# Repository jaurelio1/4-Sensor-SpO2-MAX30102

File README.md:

# 8-Modulo-I2C-OLED
Repositório da disciplina de Sistemas Embarcados do projeto de 8 Modulo I2C OLED

Alunos:

José Aurélio

Wesley Palmeira

Eduardo Donato

O projeto tem o intuito de desenvolver um despertador fazendo o uso dos módulos I2C OLED e RTC DS3231 Utilizando o RTC(Real Time Clock) DS3231 que é um relógio em tempo real de alta precisão e baixo consumo de energia, podendo fornecer informações de hora, segundos, dia, mês e ano, junto com uma bateria CR2032 para permitir o armazenamentos dos dados mesmo com a falta de energia, evitando que dados sejam perdidos; O ATmega32u4 como microcontrolador; o SSD1306 display OLED com o módulo I2C;

Utilizaremos como base as bibliotecas colocadas na pasta libraries para desenvolver a nossa (conexão do ATmega32u4, com o Display OLED e o RTC DS3231)

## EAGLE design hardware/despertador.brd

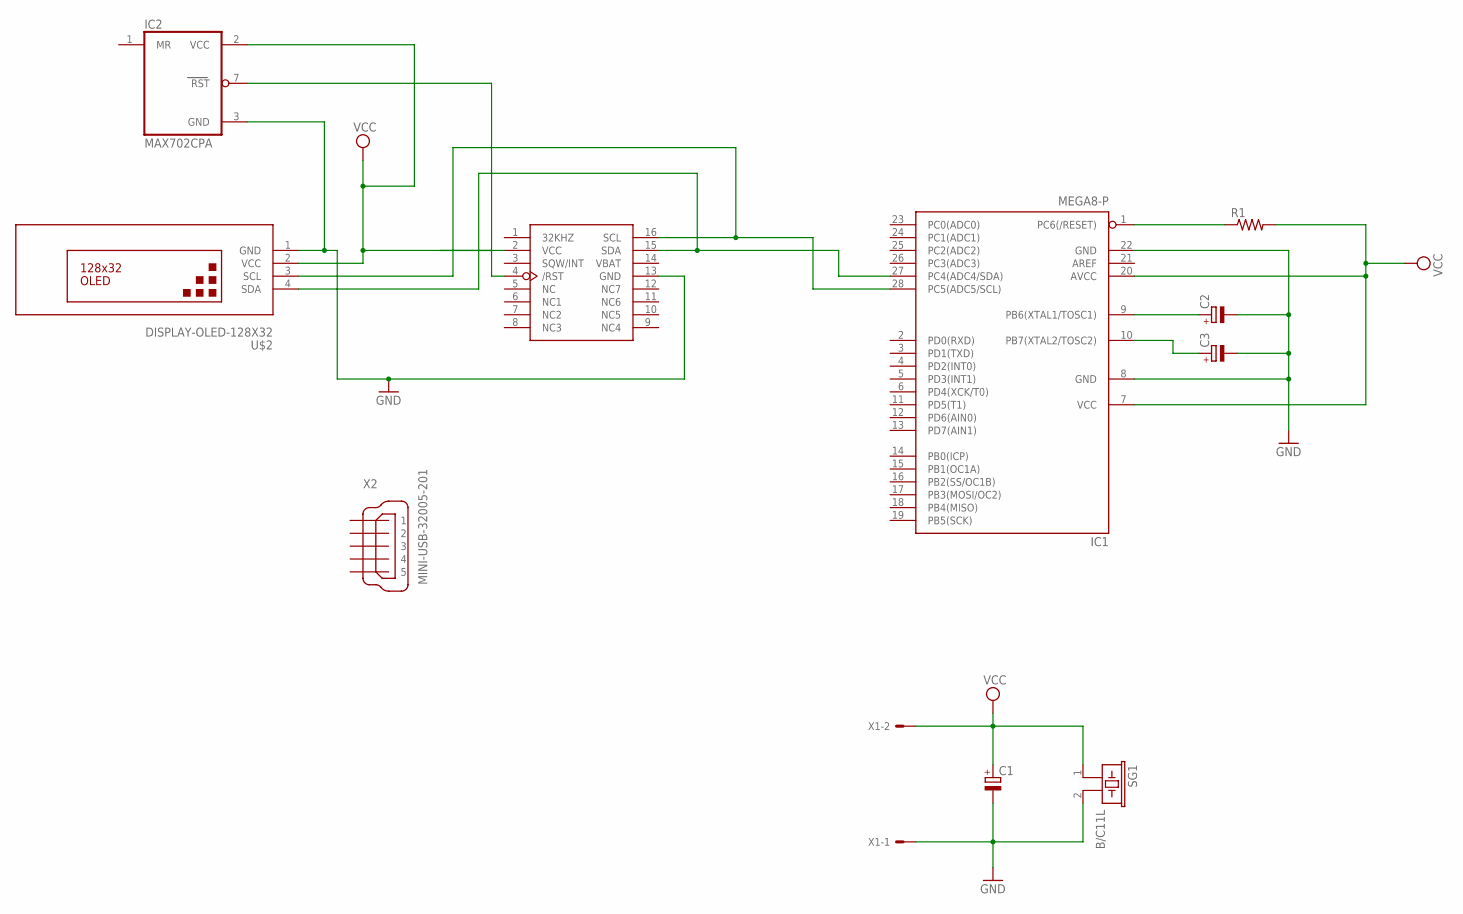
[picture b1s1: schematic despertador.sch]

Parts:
C1, C2, C3: CPOL-EUE2.5-6; E2,5-6
IC1: MEGA8-P; DIL28-3
IC2: MAX702CPA; DIL08
R1: R-US_0207/10; 0207/10
SG1: B/C11L
U$2: DISPLAY-OLED-128X32
U$3: DS3231; PDIP
X1: KK-156-2
X2: MINI-USB-32005-201; 32005-201

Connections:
GND: C1.-, C2.-, C3.-, IC1.8 (GND), IC1.22 (GND), IC2.3 (GND), SG1.2, U$2.1 (GND), U$3.13 (GND), X1.1
unnamed: IC1.27 (PC4(ADC4/SDA)), U$2.4 (SDA), U$3.15 (SDA)
unnamed: C2.+, IC1.9 (PB6(XTAL1/TOSC1))
unnamed: C3.+, IC1.10 (PB7(XTAL2/TOSC2))
unnamed: IC1.1 (PC6(/RESET)), R1.1
unnamed: IC1.28 (PC5(ADC5/SCL)), U$2.3 (SCL), U$3.16 (SCL)
unnamed: IC2.7 (RST), U$3.4 (/RST)
VCC: C1.+, IC1.7 (VCC), IC1.20 (AVCC), IC2.2 (VCC), R1.2, SG1.1, U$2.2 (VCC), U$3.2 (VCC), X1.2

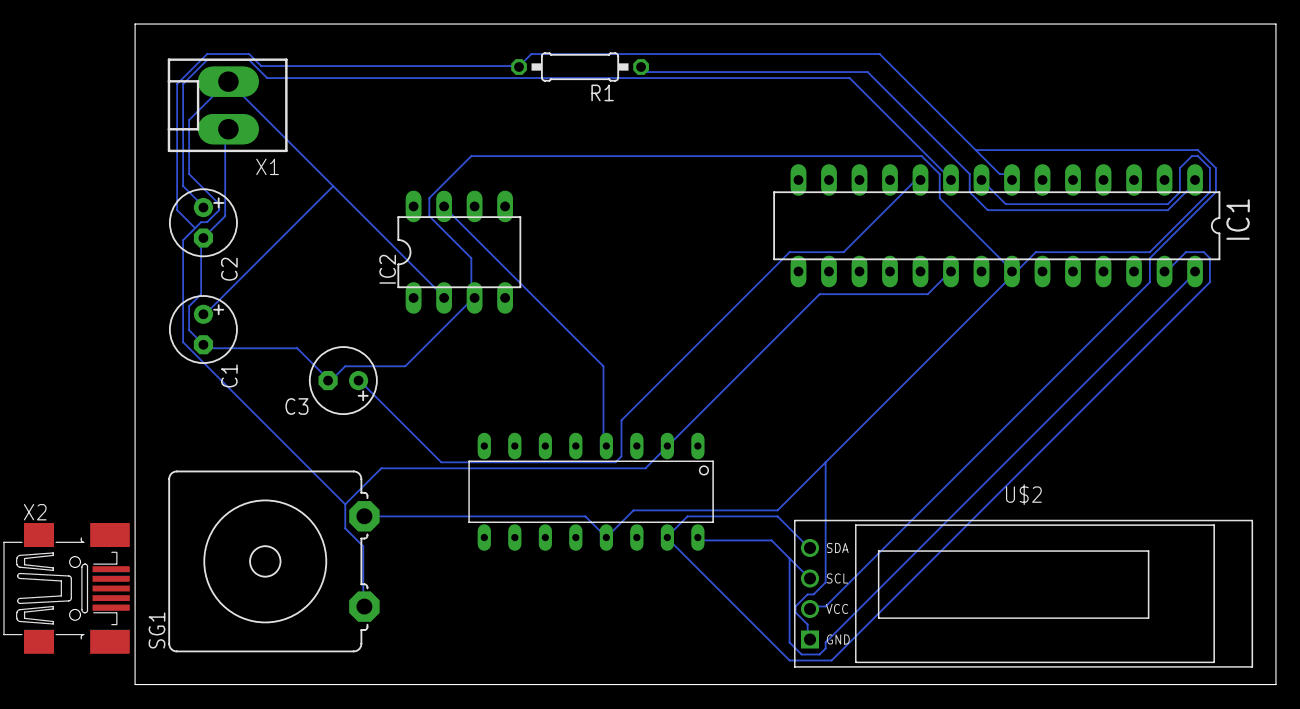
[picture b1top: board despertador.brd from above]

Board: 2 copper layers, 95.0 x 55.0 mm, 11 parts (0 on the bottom side), 8 nets.

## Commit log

2021-08-06 Adicionado diretorios e datasheet do oled
2021-08-06 Adicionado novos diretorios
2021-08-08 libraries and datasheets
2021-08-08 folders structure
2021-09-22 hello world platformio
2021-09-22 libraries
2021-09-22 example
2021-09-27 entrega parcial
2021-09-28 Create UML - Diagrama
2021-09-28 Atualizar nome
2021-09-28 Adicionado arquivos de hardware do sistema
2021-10-19 Adicionado case de sistemas

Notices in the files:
parts and their libraries:
diy-modules: Released under the Creative Commons Attribution 4.0 International License: http://creativecommons.org/licenses/by/4.0
